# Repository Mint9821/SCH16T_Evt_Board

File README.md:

# SCH16T_Evt_Board

Murata製IMUであるSCH16Tシリーズの開発ボード

## システム構成図
本基板のシステム構成図を次に示す。

### 電源構成
USB-TypeCから5Vを給電でき、1SのLiPoバッテリを充電する機能を有する。
LiPoバッテリの充電中は、USBからの給電でマイコン及びIMUは駆動する。
LiPoバッテリが接続された状態でUSBを抜くと、LiPoバッテリからの給電に切り替わる。
5Vまたは3.7Vは低損失LDOによって3.3Vまで降圧される。

### 通信
マイコンとIMUはSPI通信で接続される。
また、マイコンからUSB-TypeCにはUSB通信で接続される。
マイコンにプログラムを書き込む場合は、USB-TypeCとPCを接続して行う。

## 1S LiPoバッテリの充電回路
先述した通り、USBコネクタを接続している間はLiPoバッテリが給電される。
回路動作の確認にはLTSpiceを用いて検証した。

USB接続時の波形は次の通りである。
USB VBATが5Vを給電している場合、OUTPUTは約5Vを出力しており、V(n001)は約3.7Vになっている。
なお、実回路状ではV(n001)はLiPoバッテリの充電状況で変動する。
今回使用するバッテリ充電IC”MCP73831”の最大充電電圧は4.2Vである。

LiPoバッテリ接続時(USBコネクタ非接続)の波形は次の通りである。
OUTPUTは約3.7Vを出力しており、V(n001)は約3.7Vになっている。

## IMU周辺回路
IMUであるMurata製SCH16Tシリーズの周辺回路は、公式サイトのアプリケーションノート(SCH16T series chip carrier PCB spesification)に従う。
>https://www.murata.com/-/media/webrenewal/products/sensor/pdf/specification/sch16t-pcb-specification.ashx?la=ja-jp&cvid=20240628010000000000

## 回路図
全体回路図を次に示す。
画像が見ずらい場合は、「sch16t_evt/schematic」内のPDFを参照のこと。

## ピンレイアウト
ピンアウトを下記の表に示す。
なお、ピン番号:5の+5Vは給電用であり、LiPoバッテリが接続されていても充電はされない。LiPoバッテリの接続中にピン番号:5への給電は非推奨。

| ピン番号 | ピンアサイン |
| ---- | ---- |
| 1 | ESP32 UART RX1(RXD0) |
| 2 | ESP32 UART TX1(TXD0) |
| 3 | PPS(IO14) |
| 4 | ESP32 GPIO(IO15) |
| 5 | +5V |
| 6 | GND |
| 7 | ESP32 UART TX2(IO5) |
| 8 | ESP32 UART RX2(IO4) |

## 発注する場合
基板の製造および、部品実装に必要なデータは「sch16t_evt/SCH16T_evt_board_ver_1_1」に保存されている。
JLCPCBのみ対応しており、SCH16Tだけは現状自分で用意する必要がある。
それ以外の部品は、JLCPCBAに対応する(2025年4月時点)。

## KiCadライブラリ
本開発ボードではKiCadの既存ライブラリに加えて、SCH16XXとESP32-C6-MINI-1-N4を使用しています。
KiCadファイルを編集する際は、各自でライブラリを適用してください。

### SCH16XX
自作です、じゆうにつかっていいよ(一応、MITライセンスに従います)。

>MIT License
>
>Copyright (c) [2024] [Mint9821]
>
>Permission is hereby granted, free of charge, to any person obtaining a copy
of this library and associated files, to deal in the library without restriction, including without limitation the rights to use, copy, modify, merge, publish, distribute, sublicense, and/or sell copies of the library...

### ESP32-C6-MINI-1-N4
公開されているライブラリを使用。
KiCadの回路図およびPCBを開く際は下記URLからライブラリをダウンロードした後に適用してください。

>https://www.snapeda.com/parts/ESP32-C6-MINI-1-N4/Espressif%20Systems/view-part/

>このリポジトリには、SnapMagic Search, Inc. が提供するモデルを含んでいます。
モデルの使用にあたっては、[SnapMagic Model License](URL) に従ってください。
モデル単体での再配布は禁止されています。

### その他ライブラリ

>本設計はKiCad公式ライブラリを使用しています。
ライブラリはCC BY-SA 4.0のライセンスの下に配布されています。
https://creativecommons.org/licenses/by-sa/4.0/

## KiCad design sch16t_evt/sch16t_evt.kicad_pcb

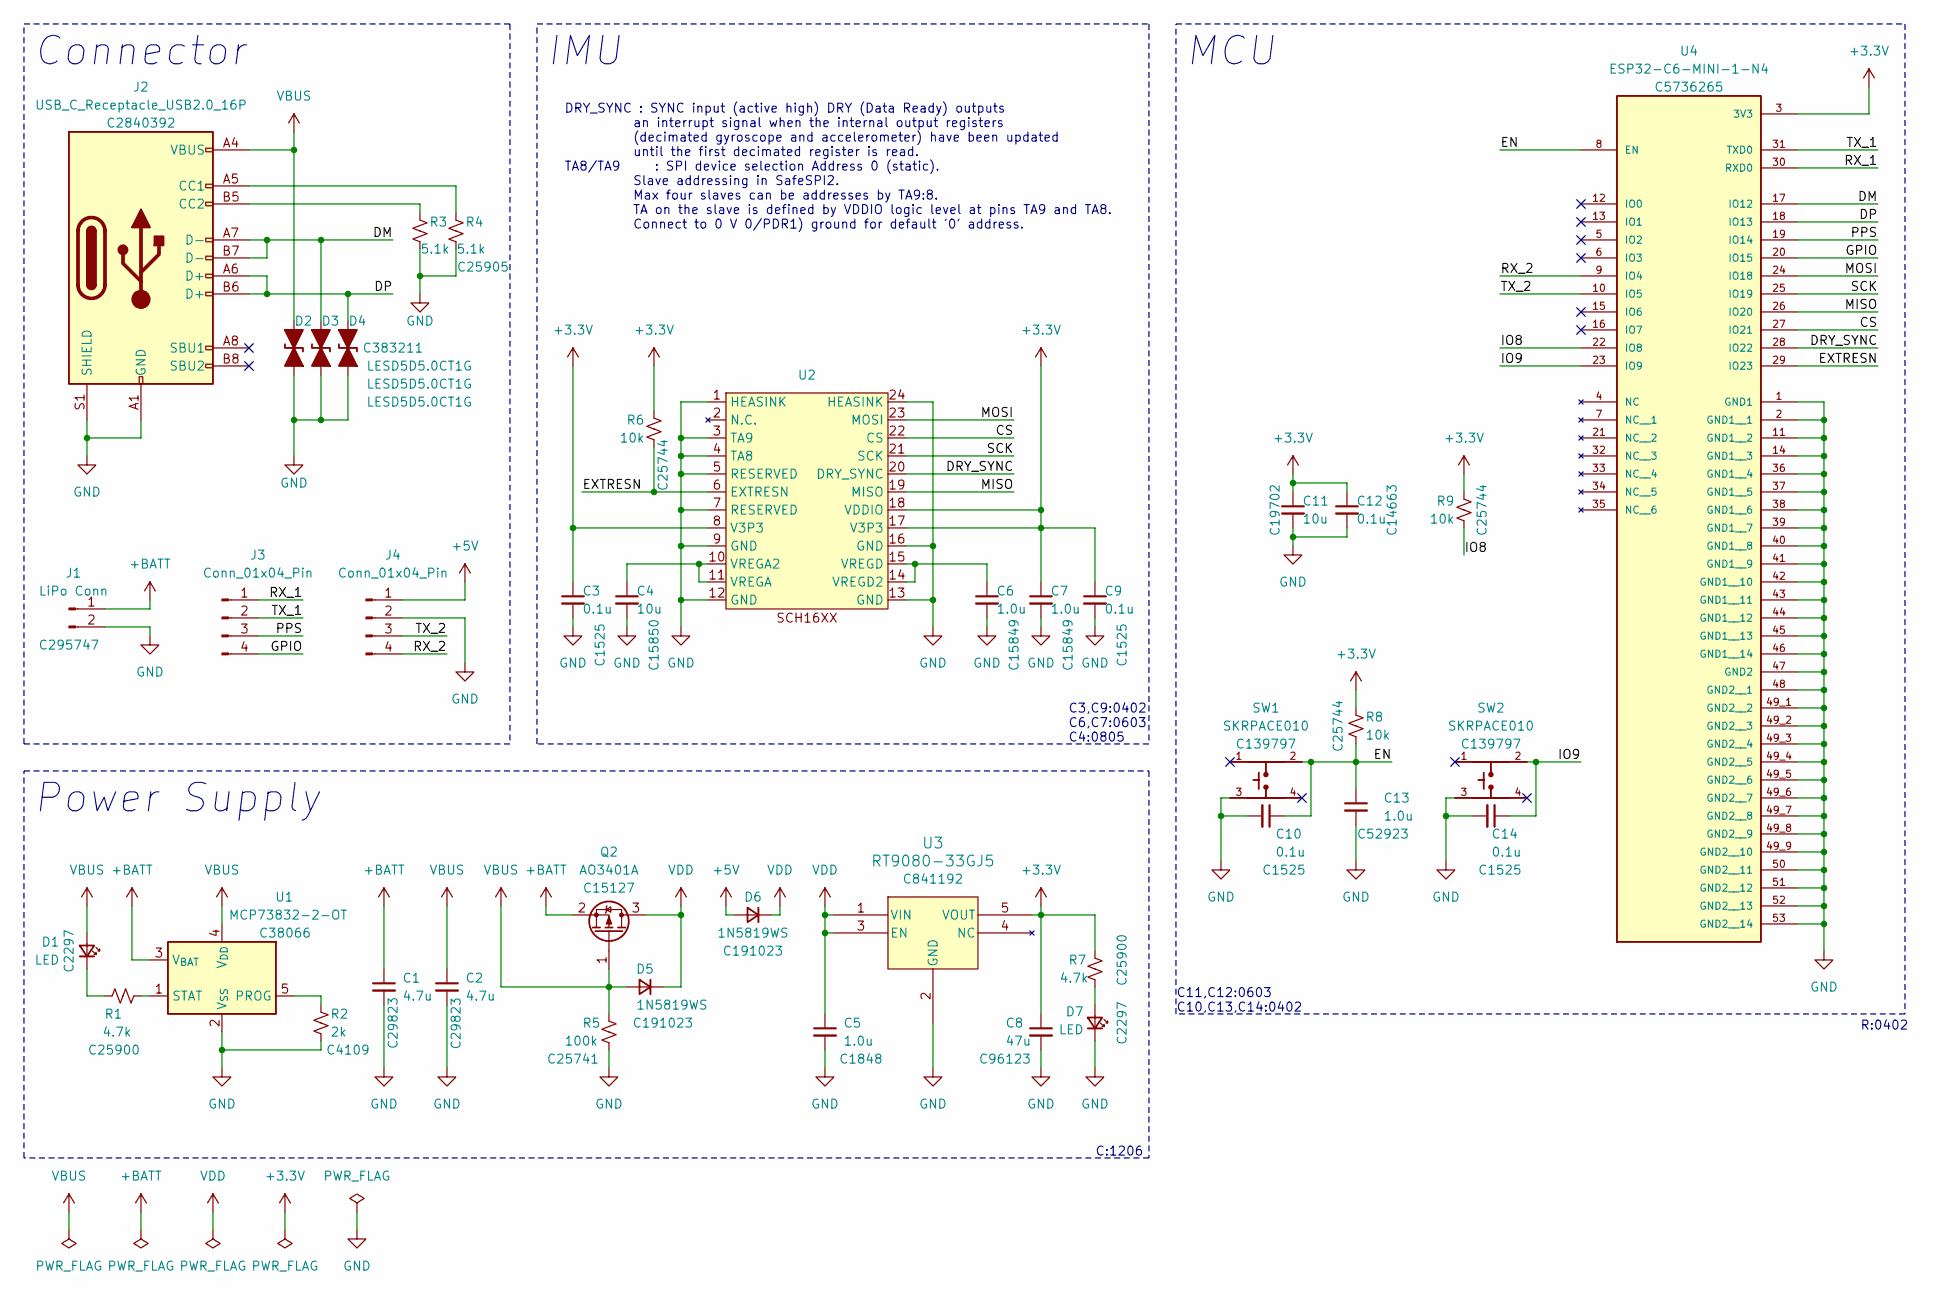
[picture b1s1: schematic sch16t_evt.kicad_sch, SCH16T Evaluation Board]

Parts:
C1, C2: 4.7u; C_1206_3216Metric; LCSC C29823
C3, C9, C10, C14: 0.1u; C_0402_1005Metric; LCSC C1525
C4: 10u; C_0805_2012Metric; LCSC C15850
C5: 1.0u; C_1206_3216Metric; LCSC C1848
C6, C7: 1.0u; C_0603_1608Metric; LCSC C15849
C8: 47u; C_1206_3216Metric; LCSC C96123
C11: 10u; C_0603_1608Metric; LCSC C19702
C12: 0.1u; C_0603_1608Metric; LCSC C14663
C13: 1.0u; C_0402_1005Metric; LCSC C52923
D1, D7: LED; D_0805_2012Metric; LCSC C2297
D2, D3, D4: LESD5D5.0CT1G; D_SOD-523; LCSC C383211
D5, D6: 1N5819WS; D_SOD-323; LCSC C191023
J1: LiPo Conn; JST_PH_S2B-PH-SM4-TB_1x02-1MP_P2.00mm_Horizontal; LCSC C295747
J2: USB_C_Receptacle_USB2.0_16P; USB_C_Receptacle_GCT_USB4110; LCSC C2840392
J3, J4: Conn_01x04_Pin; PinHeader_1x04_P2.54mm_Vertical
Q2: AO3401A; SOT-23; LCSC C15127
R1, R7: 4.7k; R_0402_1005Metric; LCSC C25900
R2: 2k; R_0402_1005Metric; LCSC C4109
R3, R4: 5.1k; R_0402_1005Metric; LCSC C25905
R5: 100k; R_0402_1005Metric; LCSC C25741
R6, R8, R9: 10k; R_0402_1005Metric; LCSC C25744
SW1, SW2: SKRPACE010; SW_SKRPACE010; LCSC C139797
U1: MCP73832-2-OT; SOT-23-5; LCSC C38066
U2: SCH16XX
U3: RT9080-33GJ5; SOT-23-5; LCSC C841192
U4: ESP32-C6-MINI-1-N4; XCVR_ESP32-C6-MINI-1-N4; PARTREV 1.0; LCSC C5736265

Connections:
+3.3V: C3.1, C7.1, C8.1, C9.1, C11.1, C12.1, R6.2, R7.1, R8.1, R9.2, U2.8 (V3P3), U2.17 (V3P3), U2.18 (VDDIO), U3.5 (VOUT), U4.3 (3V3)
+5V: D6.2 (A), J4.1
+BATT: C1.1, J1.1, Q2.2 (S), U1.3 (V_{BAT})
/CS: U2.22 (CS), U4.27 (IO21)
/DM: D3.2 (A2), J2.A7 (D-), J2.B7 (D-), U4.17 (IO12)
/DP: D4.2 (A2), J2.A6 (D+), J2.B6 (D+), U4.18 (IO13)
/DRY_SYNC: U2.20 (DRY_SYNC), U4.28 (IO22)
/EN: C10.1, C13.1, R8.2, SW1.2, U4.8 (EN)
/EXTRESN: R6.1, U2.6 (EXTRESN), U4.29 (IO23)
/GPIO: J3.4, U4.20 (IO15)
/IO8: R9.1, U4.22 (IO8)
/IO9: C14.1, SW2.2, U4.23 (IO9)
/MISO: U2.19 (MISO), U4.26 (IO20)
/MOSI: U2.23 (MOSI), U4.24 (IO18)
/PPS: J3.3, U4.19 (IO14)
/RX_1: J3.1, U4.30 (RXD0)
/RX_2: J4.4, U4.9 (IO4)
/SCK: U2.21 (SCK), U4.25 (IO19)
/TX_1: J3.2, U4.31 (TXD0)
/TX_2: J4.3, U4.10 (IO5)
GND: C1.2, C2.2, C3.2, C4.2, C5.2, C6.2, C7.2, C8.2, C9.2, C10.2, C11.2, C12.2, C13.2, C14.2, D2.1 (A1), D3.1 (A1), D4.1 (A1), D7.1 (K), J1.2, J2.A1 (GND), J2.A12 (GND), J2.B1 (GND), J2.B12 (GND), J2.S1 (SHIELD), J4.2, R2.2, R3.2, R4.2, R5.2, SW1.3, SW2.3, U1.2 (V_{SS}), U2.1 (HEASINK), U2.3 (TA9), U2.4 (TA8), U2.5 (RESERVED), U2.7 (RESERVED), U2.9 (GND), U2.12 (GND), U2.13 (GND), U2.16 (GND), U2.24 (HEASINK), U3.2 (GND), U4.1 (GND1), U4.2 (GND1__1), U4.11 (GND1__2), U4.14 (GND1__3), U4.36 (GND1__4), U4.37 (GND1__5), U4.38 (GND1__6), U4.39 (GND1__7), U4.40 (GND1__8), U4.41 (GND1__9), U4.42 (GND1__10), U4.43 (GND1__11), U4.44 (GND1__12), U4.45 (GND1__13), U4.46 (GND1__14), U4.47 (GND2), U4.48 (GND2__1), U4.49_1 (GND2__2), U4.49_2 (GND2__3), U4.49_3 (GND2__4), U4.49_4 (GND2__5), U4.49_5 (GND2__6), U4.49_6 (GND2__7), U4.49_7 (GND2__8), U4.49_8 (GND2__9), U4.49_9 (GND2__10), U4.50 (GND2__11), U4.51 (GND2__12), U4.52 (GND2__13), U4.53 (GND2__14)
unnamed: D1.1 (K), R1.1
unnamed: D7.2 (A), R7.2
unnamed: J2.A5 (CC1), R4.1
unnamed: J2.B5 (CC2), R3.1
unnamed: R2.1, U1.5 (PROG)
unnamed: R1.2, U1.1 (STAT)
unnamed: C4.1, U2.10 (VREGA2), U2.11 (VREGA)
unnamed: C6.1, U2.14 (VREGD2), U2.15 (VREGD)
VBUS: C2.1, D1.2 (A), D2.2 (A2), D5.2 (A), J2.A4 (VBUS), J2.A9 (VBUS), J2.B4 (VBUS), J2.B9 (VBUS), Q2.1 (G), R5.1, U1.4 (V_{DD})
VDD: C5.1, D5.1 (K), D6.1 (K), Q2.3 (D), U3.1 (VIN), U3.3 (EN)

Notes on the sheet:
Power Supply
MCU
IMU
DRY_SYNC : SYNC input (active high) DRY (Data Ready) outputs an interrupt signal when the internal output registers (decimated gyroscope and accelerometer) have been updated until the first decimated register is read. TA8/TA9 : SPI device selection Address 0 (static). Slave addressing in SafeSPI2. 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
Connector
C:1206
C11,C12:0603 C10,C13,C14:0402
C3,C9:0402 C6,C7:0603 C4:0805
R:0402

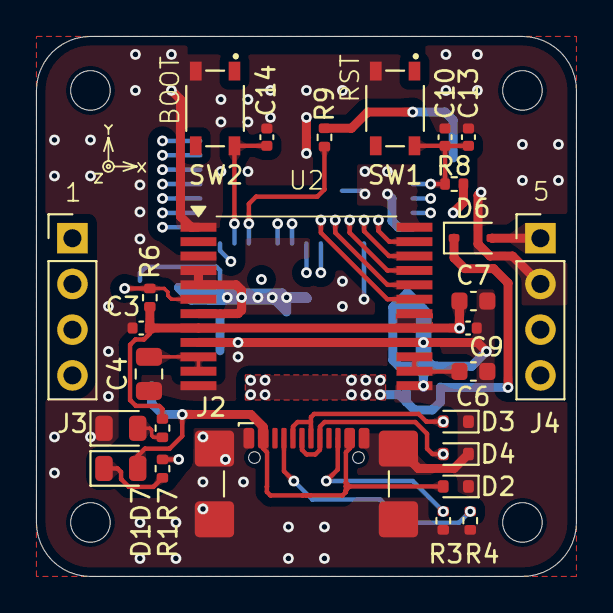
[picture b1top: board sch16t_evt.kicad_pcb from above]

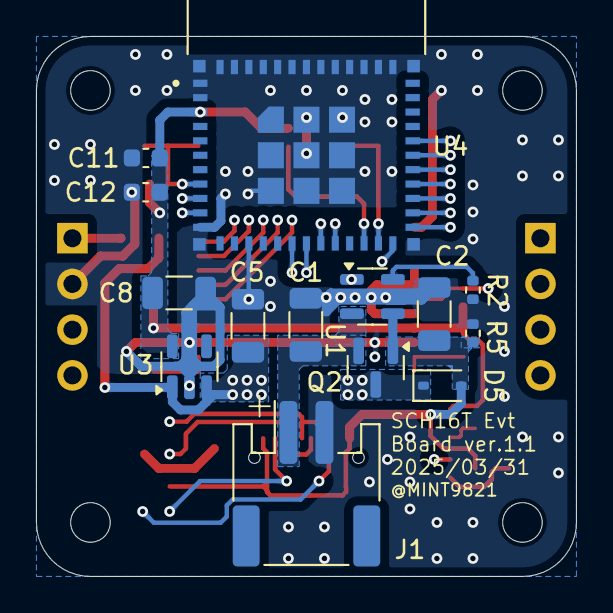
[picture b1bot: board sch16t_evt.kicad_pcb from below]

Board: 4 copper layers, 30.0 x 30.0 mm, 41 parts (14 on the bottom side), 31 nets.

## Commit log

2025-04-23 Readme編集
2025-04-23 Kicad files
2025-04-23 chenage LiPo_charge_files and Readme
2025-04-27 Readme updata
2025-04-27 add fig
